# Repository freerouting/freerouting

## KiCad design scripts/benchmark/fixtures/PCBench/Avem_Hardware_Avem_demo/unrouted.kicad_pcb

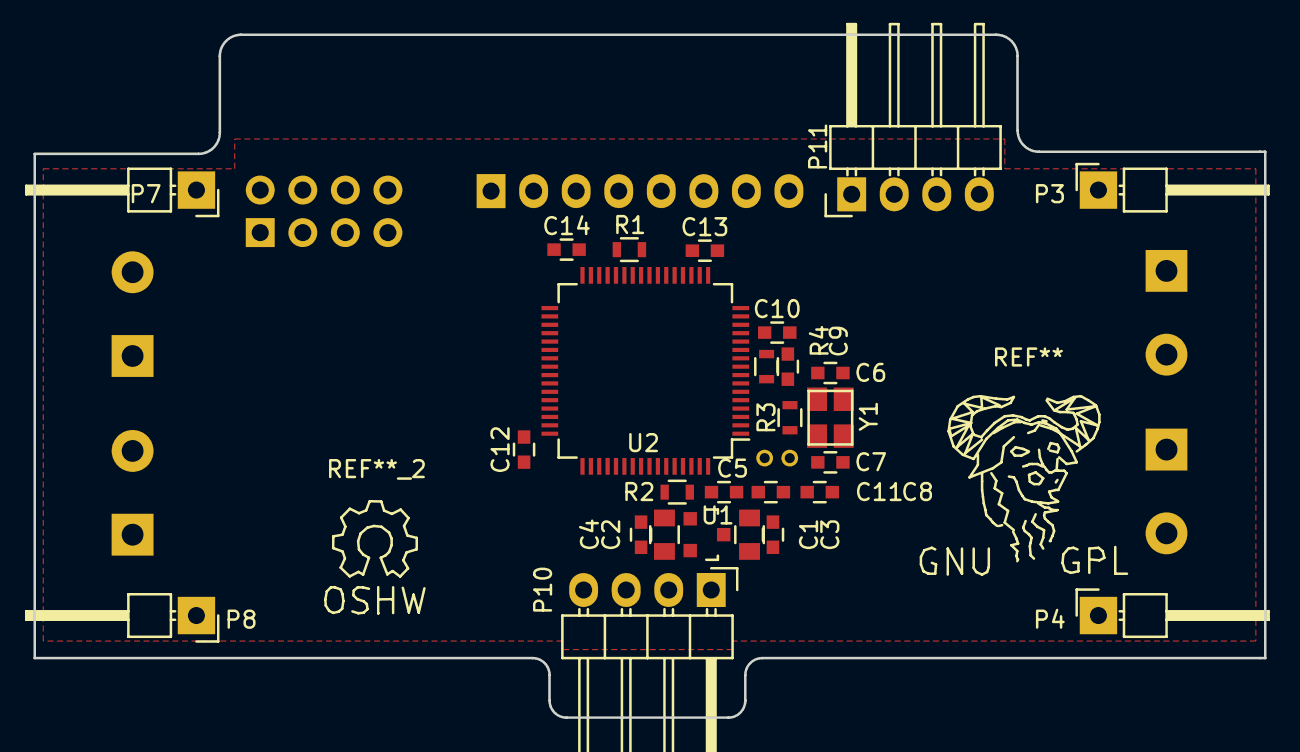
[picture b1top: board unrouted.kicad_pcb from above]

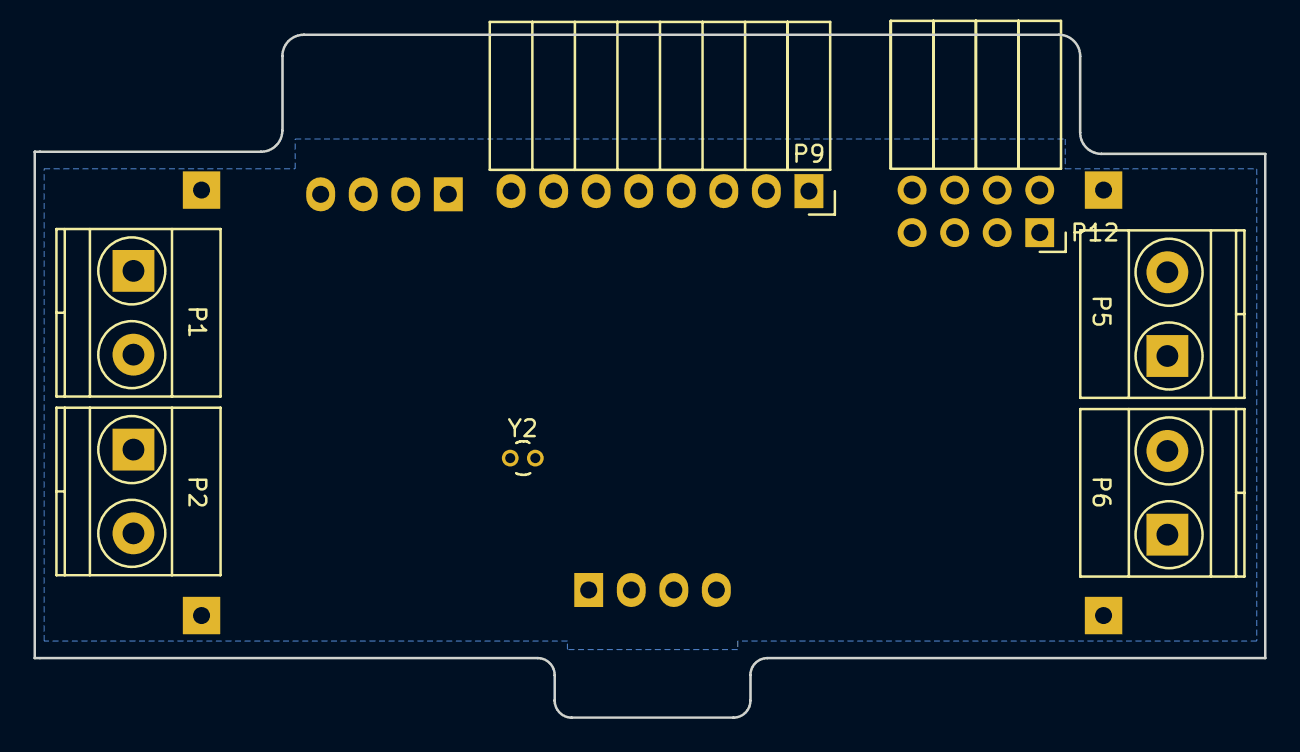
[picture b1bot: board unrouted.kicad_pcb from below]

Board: 2 copper layers, 73.5 x 40.8 mm, 34 parts (7 on the bottom side), 22 nets, no tracks yet.

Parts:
C1, C2: C_0805
C3, C4, C5, C6, C7, C8, C9, C10, C11, C12, C13, C14: C_0603
P1, P2, P5, P6: TerminalBlock_Pheonix_MKDS1.5-2pol
P3, P4, P7, P8: Pin_Header_Angled_1x01
P9: Socket_Strip_Angled_1x08
P10: ISP; Pin_Header_Angled_1x04
P11: Pin_Header_Angled_1x04
P12: Socket_Strip_Angled_2x04
R1, R2, R3, R4: R_0603
U1: SOT-23
U2: STM32F103RCT6; LQFP-64_10x10mm_Pitch0.5mm
Y1: crystal_FA238-TSX3225
Y2: Crystal_Round_Vertical_2mm

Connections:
3V3: C2.1, C4.2, C5.1, C10.1, C12.1, C13.1, C14.1, P9.1, P11.1, P12.3, P12.7, R4.1, U1.2, U2.1, U2.13, U2.19, U2.32, U2.48, U2.64
+3V3: C1.1, C3.2, P1.1, P2.1, P5.1, P6.1, P10.1, U1.3
BLDC1: P3.1, U2.22
BLDC2: P4.1, U2.23
BLDC3: P7.1, U2.26
BLDC4: P8.1, U2.27
BOOT0: R2.2, U2.60
BOOT1: R1.2, U2.28
GND: C1.2, C2.2, C3.1, C4.1, C5.2, C6.2, C7.2, C8.2, C9.2, C10.2, C11.2, C12.2, C13.2, C14.2, P1.2, P2.2, P5.2, P6.2, P9.2, P9.7, P10.2, P11.2, P12.2, R1.1, U1.1, U2.12, U2.18, U2.31, U2.47, U2.63
OSCIN: C7.1, R3.2, U2.5, Y1.2
OSCIN32: C11.1, U2.3, Y2.2
OSCOUT: C6.1, R3.1, U2.6, Y1.1
OSCOUT32: C8.1, U2.4, Y2.1
RESET: C9.1, R4.2, U2.7
RX1: P10.3, U2.43
RX2: P11.3, U2.17
RX3: P12.8, U2.30
SCL: P9.3, U2.36
SDA: P9.4, U2.35
TX1: P10.4, U2.42
TX2: P11.4, U2.16
TX3: P12.1, U2.29

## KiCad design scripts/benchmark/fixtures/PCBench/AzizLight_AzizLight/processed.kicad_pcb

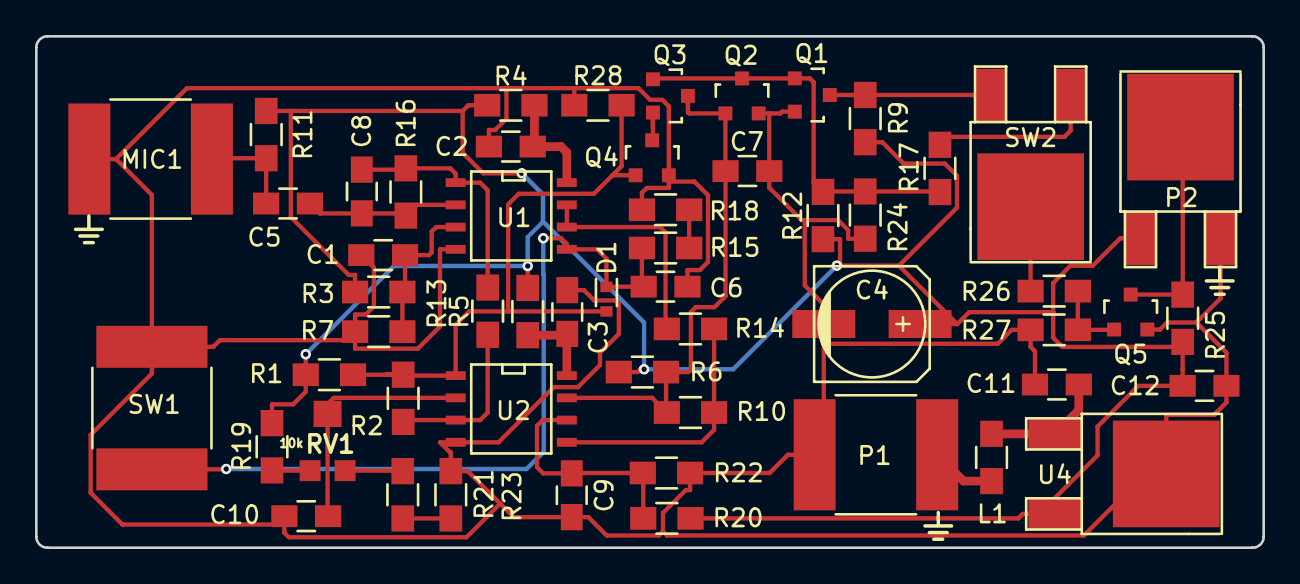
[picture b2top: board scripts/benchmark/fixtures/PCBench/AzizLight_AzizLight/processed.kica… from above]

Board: 2 copper layers, 70.1 x 29.2 mm, 55 parts (0 on the bottom side), 29 nets.

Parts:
C1, C2, C3, C5, C9, C10, C12: 0.1uF; C_0805_HandSoldering
C4: 100uF; c_elec_6.3x5.8
C6, C7: 10uF; C_0805_HandSoldering
C8: 100pF; C_0805_HandSoldering
C11: 0.33uF; C_0805_HandSoldering
D1: 1N4148; SOD-523
L1: 10uH; R_0805_HandSoldering
MIC1: POM-3535; C_2225_HandSoldering
P1: +9V; C_2225_HandSoldering
P2: Trigger Out; TO-252-2Lead
Q1, Q2, Q3, Q4, Q5: BS170; SOT-23
R1, R3, R7, R13, R19, R21, R22, R23: 10k; R_0805_HandSoldering
R2: 220k; R_0805_HandSoldering
R4, R5, R17, R26: 100; R_0805_HandSoldering
R6: 100k; R_0805_HandSoldering
R9, R12, R25: 4.7k; R_0805_HandSoldering
R10: 470k; R_0805_HandSoldering
R11: 5.6k; R_0805_HandSoldering
R14: 120k; R_0805_HandSoldering
R15, R18: 10M; R_0805_HandSoldering
R16: 560k; R_0805_HandSoldering
R20: 12k; R_0805_HandSoldering
R24, R27, R28: 1M; R_0805_HandSoldering
RV1: 10k; TRIMPOT_SMD
SW1: Reset; C_2225_HandSoldering
SW2: Invert; TO-252-2Lead
U1: MCP602; SOIC-8-N
U2: LM393; SOIC-8-N
U4: MC7805; TO-252-2Lead

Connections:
+5V: C4.1, C12.1, P2.1, R1.2, R3.1, R4.1, R5.1, R6.1, R9.1, R11.1, R12.1, R19.2, R20.1, R25.1, U4.3
GND: C1.2, C2.1, C3.1, C4.2, C6.2, C7.2, C9.2, C10.2, C11.2, C12.2, MIC1.2, P1.1, P2.3, Q1.2, Q2.2, Q4.2, Q5.2, R7.2, R18.1, R22.1, R23.1, R24.1, R27.1, R28.1, SW1.1, U1.4, U2.4, U4.2
unnamed: C1.1, R3.2, R7.1, U1.3
unnamed: C2.2, R4.2, U1.8
unnamed: C3.2, R5.2, U2.8
unnamed: C5.1, C8.2, R16.2, U1.2
unnamed: C5.2, MIC1.1, R11.2
unnamed: C6.1, D1.1, R15.2, SW1.2, U1.5
unnamed: C7.1, Q2.1, Q3.3, R6.2, R10.1, U2.7
unnamed: C8.1, R13.2, R16.1, U1.1
unnamed: C9.1, R20.2, R22.2, U2.6
unnamed: C10.1, RV1.2, U2.2
unnamed: C11.1, L1.2, U4.1
unnamed: D1.2, Q4.1, R1.1, R2.1, R28.2, U2.1
unnamed: L1.1, P1.2
unnamed: P2.2, Q5.3, R25.2
unnamed: Q1.1, Q2.3, Q3.1, R12.2, R17.2, R24.2
unnamed: Q1.3, R9.2, SW2.3
unnamed: Q3.2, Q4.3
unnamed: Q5.1, R26.1, R27.2
unnamed: R10.2, R14.1, U2.5
unnamed: R2.2, R13.1, U2.3
unnamed: R14.2, U1.6, U1.7
unnamed: R15.1, R18.2
unnamed: R17.1, SW2.1
unnamed: R19.1, RV1.1
unnamed: R21.1, R23.2
unnamed: R21.2, RV1.3
unnamed: R26.2, SW2.2

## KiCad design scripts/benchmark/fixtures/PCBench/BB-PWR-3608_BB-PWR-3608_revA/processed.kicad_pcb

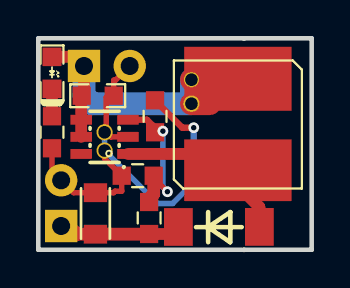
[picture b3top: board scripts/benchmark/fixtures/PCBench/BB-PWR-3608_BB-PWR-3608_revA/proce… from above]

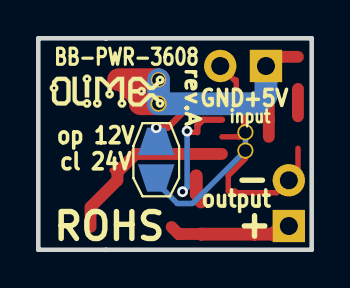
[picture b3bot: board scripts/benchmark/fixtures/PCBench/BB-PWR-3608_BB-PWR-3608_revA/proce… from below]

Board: 2 copper layers, 15.2 x 11.8 mm, 18 parts (2 on the bottom side), 7 nets.

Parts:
C1: 22uF/6.3V; C_0603
C3: 22uF/50V; R_0805
D1: LED_RED_0603; LED_0603_KA
D2: 1N5819/SS14; SOD106-R-KA
JP1: Jumper_NO_Small; JUMP_SMD
L1: CL22uH/SD75; SD75
Noname_1: LOGO_OLIMEX_80
P1, P2: HN1x2; HN1x2_Jumper
R1: 39K 1%; R_0603_DWS
R2: 1.05K 1%; R_0603_DWS
R3: 2.2K; R_0603_DWS
R4: 1K 1%; R_0603_DWS
Ref**: Val**; via_09_07
Ref**_2, Ref**_3, Ref**_4: Val**; via_09_07
U1: MT3608; SOT23-6

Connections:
GND: C1.2, C3.2, JP1.2, P1.2, P2.2, R2.2, R3.1, Ref**.0, Ref**_2.0, U1.2
unnamed: C1.1, D1.2, L1.1, P1.1, Ref**_3.0, Ref**_4.0, U1.4, U1.5
unnamed: C3.1, D2.1, P2.1, R1.1
unnamed: D1.1, R3.2
unnamed: D2.2, L1.2, U1.1
unnamed: JP1.1, R4.1
unnamed: R1.2, R2.1, R4.2, U1.3

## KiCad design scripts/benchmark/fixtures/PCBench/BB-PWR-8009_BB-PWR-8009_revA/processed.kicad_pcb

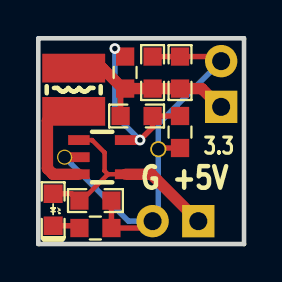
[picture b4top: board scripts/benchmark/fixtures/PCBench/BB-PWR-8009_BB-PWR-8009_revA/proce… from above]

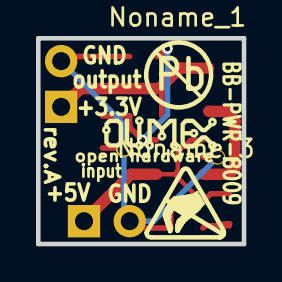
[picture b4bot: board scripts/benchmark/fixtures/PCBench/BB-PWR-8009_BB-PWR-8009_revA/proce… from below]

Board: 2 copper layers, 11.4 x 11.4 mm, 17 parts (3 on the bottom side), 6 nets.

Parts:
C1, C3, C4: 22uF/6.3V; C_0603
C2: 22pF; C_0603
D1: LED_RED_0603; LED_0603_KA
L1: 2.2uH/1.5A/JCR<0.1R/CD32; CD32
Noname_1: LOGO_PBFREE
Noname_2: LOGO_OLIMEX_80
Noname_3: LOGO_ANTISTATIC_SMALL_4.5mmX2.8mm
P1, P2: HN1x2; HN1x2_Jumper
R1: 4.99K 1%; R_0603_DWS
R2: 1.1K 1%; R_0603_DWS
R3: 2.2K; R_0603_DWS
Ref**: Val**; via_09_07
Ref**_2: Val**; via_09_07
U1: SY8009AAAC(SOT23-5); SOT-23-5

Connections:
GND: C1.2, C3.2, C4.2, P1.2, P2.2, R2.2, R3.1, Ref**.0, Ref**_2.0, U1.2
unnamed: C1.1, D1.2, P1.1, U1.1, U1.4
unnamed: C2.1, C3.1, C4.1, L1.2, P2.1, R1.1
unnamed: C2.2, R1.2, R2.1, U1.5
unnamed: D1.1, R3.2
unnamed: L1.1, U1.3
